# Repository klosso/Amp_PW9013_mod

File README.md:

Base mod for Unitra PW9013 ampituner.
Not any sufifticate thing. Just replace old transistors based eq with Ic and, add BT FM tuner.
Tuner based on FM module RD07 with RDS
Autio IC is old TSA6231.

Versions :
0.00001 preliminary alfa.

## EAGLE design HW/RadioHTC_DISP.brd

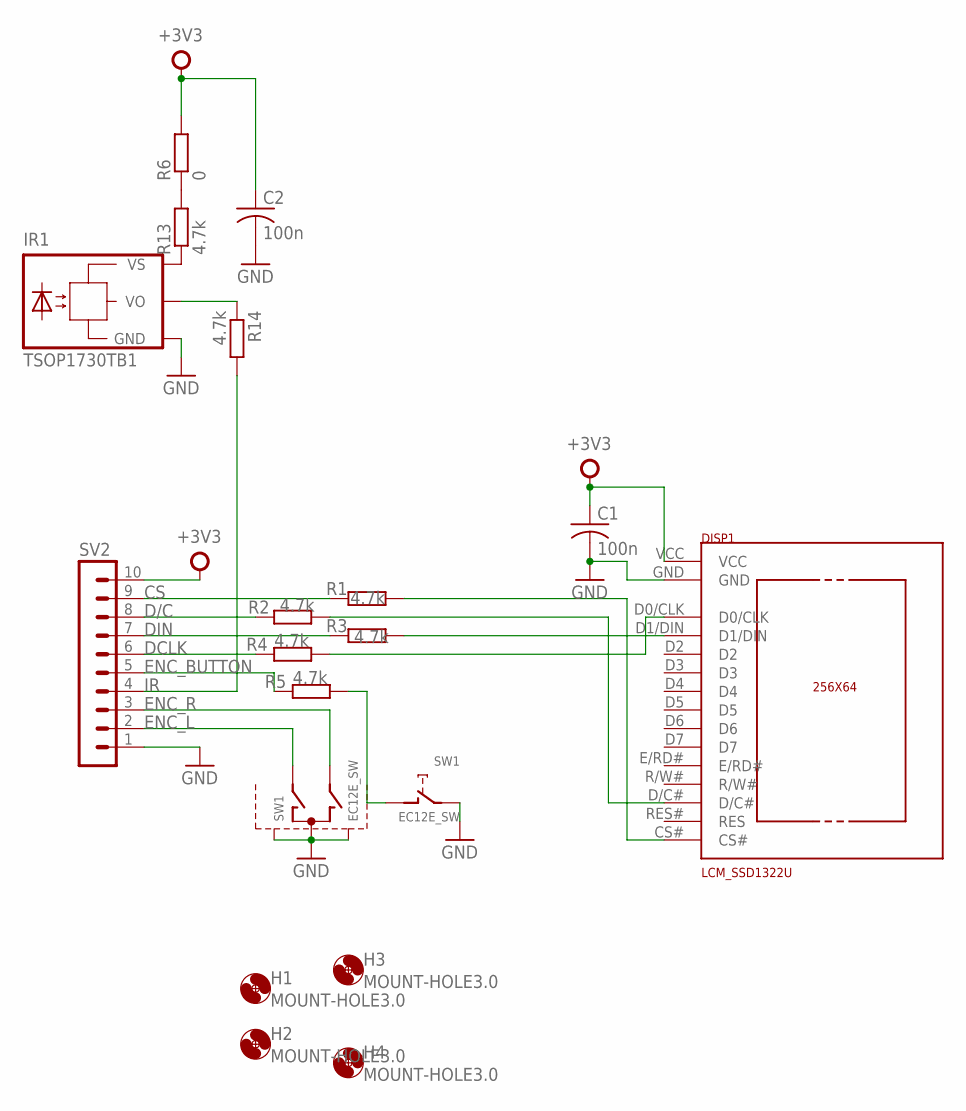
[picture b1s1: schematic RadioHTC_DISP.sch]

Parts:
C1, C2: 100n; C1206
DISP1: LCM_SSD1322U; LCM_SSD1322_VERT
H1, H2, H3, H4: MOUNT-HOLE3.0; 3,0
IR1: TSOP1730TB1; TSOP17_TB1
R1, R2, R3, R4, R5, R13, R14: 4.7k; R1206
R6: 0; R1206
SV2: MA10-1
SW1: EC12E_SW; ALPS_EC12E_SW

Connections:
+3V3: C1.1, C2.1, DISP1.VCC, R6.2, SV2.10
CS: R1.1, SV2.9
CS#: DISP1.CS#, R1.2
D/C: R2.1, SV2.8
DCLK: R4.1, SV2.6
DCLK_: DISP1.D0/CLK, R4.2
DC_: DISP1.D/C#, R2.2
DIN: R3.1, SV2.7
DIN_: DISP1.D1/DIN, R3.2
ENC_BUTTON: R5.1, SV2.5
ENC_L: SV2.2, SW1.A
ENC_R: SV2.3, SW1.B
GND: C1.2, C2.2, DISP1.GND, IR1.GND, SV2.1, SW1.C, SW1.E (2), SW1.GND@1, SW1.GND@2
IR: R14.2, SV2.4
unnamed: R5.2, SW1.D (1)
unnamed: R6.1, R13.2
unnamed: IR1.VS, R13.1
unnamed: IR1.VO, R14.1

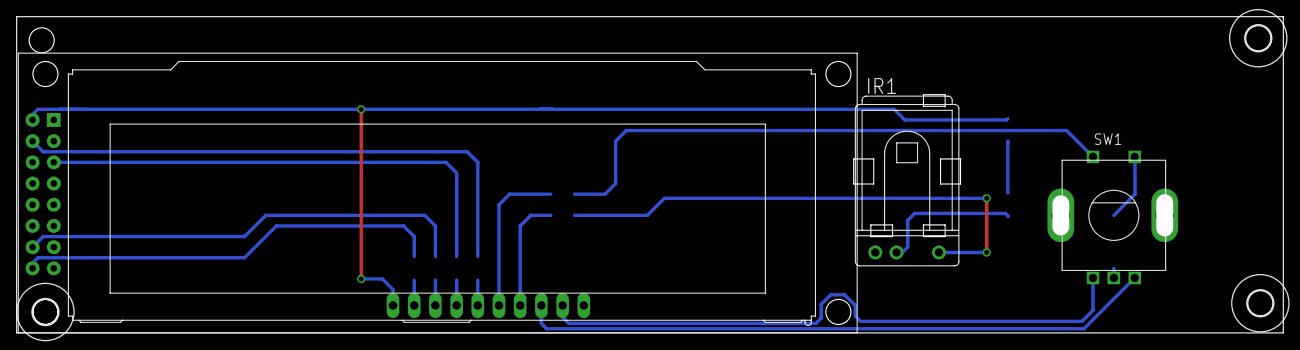
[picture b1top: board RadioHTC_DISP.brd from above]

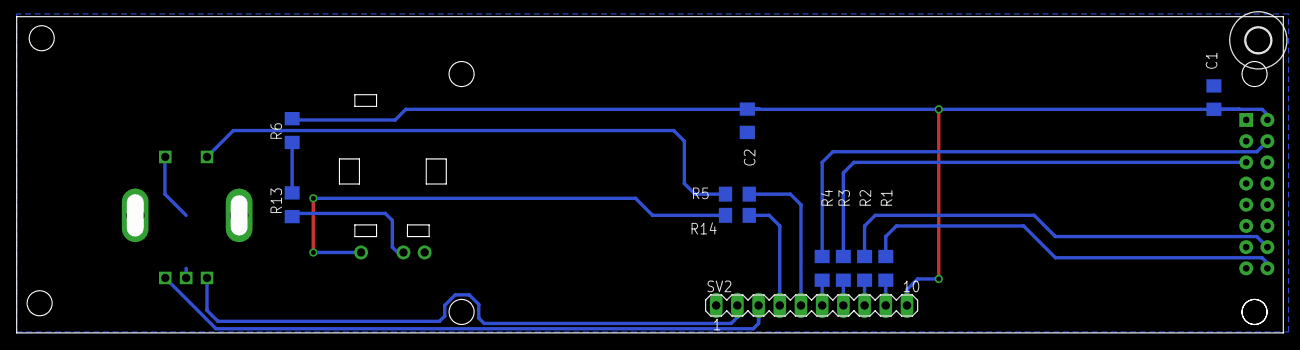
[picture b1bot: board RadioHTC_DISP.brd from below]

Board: 2 copper layers, 149.7 x 35.9 mm, 18 parts (12 on the bottom side), 18 nets.

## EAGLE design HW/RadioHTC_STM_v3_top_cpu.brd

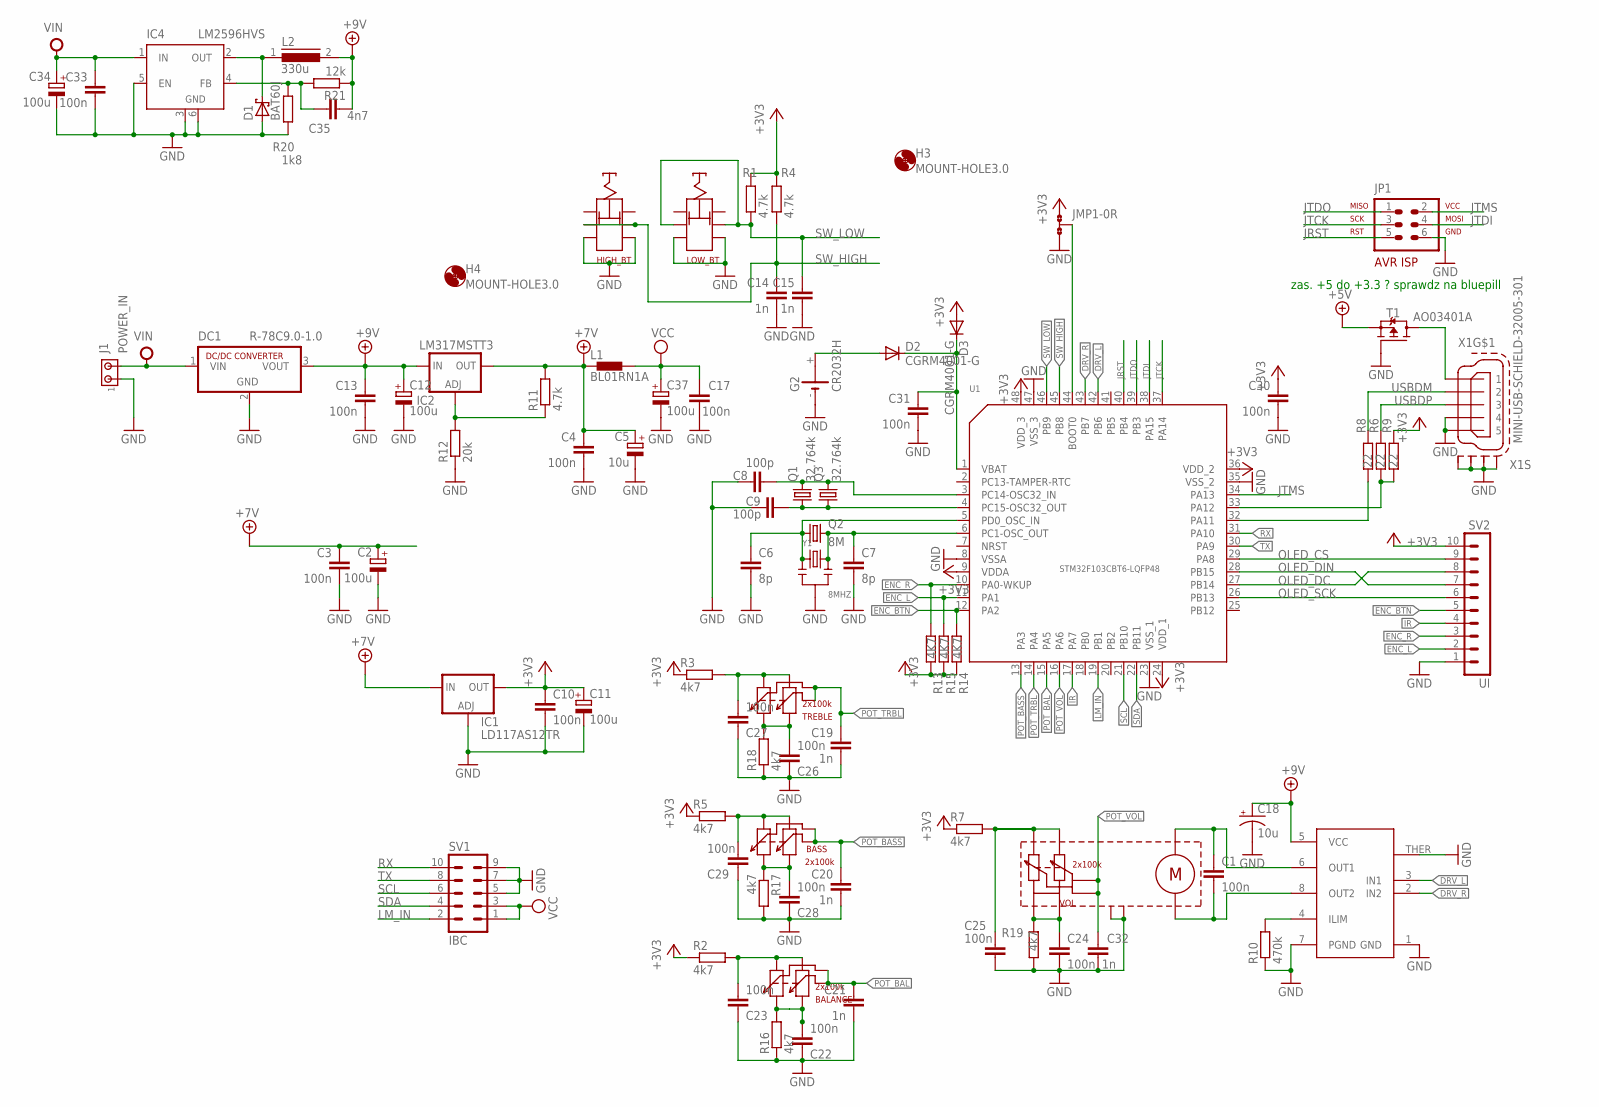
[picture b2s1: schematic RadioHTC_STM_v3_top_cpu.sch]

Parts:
BALANCE: 2x100k; POT_VERT_DOUBLE
BASS: 2x100k; POT_VERT_DOUBLE
C1, C3, C4, C10, C13, C17, C22, C23, C24, C25, C26, C27, C28, C29, C30, C31, C33: 100n; C1206
C2, C11, C34: 100u; E2-5
C5: 10u; E2-5
C6, C7: 8p; C0805K
C8, C9: 100p; C0805K
C12: 100u; 153CLV-0605
C14, C15, C19, C20, C21, C32: 1n; C1206
C18: 10u; 153CLV-0810
C35: 4n7; C1206
C37: 100u; 153CLV-0405
D1: BAT60J; SOD323_ST
D2, D3: CGRM4001-G; SOD-123_MINI-SMA
DC1: R-78C9.0-1.0; SIP3
G2: CR2032H
H3, H4: MOUNT-HOLE3.0; 3,0
IC1: LD117AS12TR; SOT223
IC2: LM317MSTT3; SOT223
IC4: LM2596HVS; TO263-5
J1: POWER_IN; 1X2MTA
JMP1: 0R-JUMPA; A0R-JMP
JP1: AVR-ISP-6VERT; AVR-ISP-6
L1: BL01RN1A
L2: 330u; DR74
Q1: 32.764k; MM39SL
Q2: 8M; HC49U-V
Q3: 32.764k; MM20SS
R1, R4, R11: 4.7k; R1206
R2, R3, R5, R7, R16, R17, R18, R19: 4k7; R1206
R6, R8, R9: 22; R1206
R10: 470k; R1206
R12: 20k; R1206
R13, R14, R15: 4K7; R1206
R20: 1k8; R1206
R21: 12k; R1206
SV1: IBC; ML10
SV2: UI; MA10-1W
SW4: LOW_BT; ISO3
SW6: HIGH_BT; ISO3
T1: AO03401A; SOT23-R
TREBLE: 2x100k; POT_VERT_DOUBLE
U1: STM32F103CBT6-LQFP48; LQFP48-0.5-7X7MM
U2: DRV8871
VOL: 2x100k; POT_DOUBLE_MOTOR
X1: MINI-USB-SCHIELD-32005-301; 32005-301
Y1: 8MHZ; X3-SMD-3.6X1.3X0.8MM

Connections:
+3V3: C10.1, C11.+, C30.1, D3.A, IC1.4 (OUT), JMP1.1, R1.2, R2.1, R3.1, R4.2, R5.1, R7.1, R9.2, R13.2, R14.2, R15.2, SV2.10, U1.9 (VDDA), U1.24 (VDD_1), U1.36 (VDD_2), U1.48 (VDD_3)
+5V: T1.2 (S)
+7V: C2.+, C3.1, C4.1, C5.+, IC1.3 (IN), IC2.4 (OUT), L1.1, R11.2
+9V: C12.+, C13.1, C18.+, C35.2, DC1.3 (VOUT), IC2.3 (IN), L2.2, R21.1, U2.5 (VCC)
DRV_L: U1.42 (PB6), U2.3 (IN1)
DRV_R: U1.43 (PB7), U2.2 (IN2)
ENC_BTN: R14.1, SV2.5, U1.12 (PA2)
ENC_L: R15.1, SV2.2, U1.11 (PA1)
ENC_R: R13.1, SV2.3, U1.10 (PA0-WKUP)
GND: C2.-, C3.2, C4.2, C5.-, C6.2, C7.2, C8.2, C9.1, C10.2, C11.-, C12.-, C13.2, C14.2, C15.2, C17.2, C18.-, C19.2, C20.2, C21.2, C22.1, C23.1, C24.1, C25.1, C26.1, C27.1, C28.1, C29.1, C30.2, C31.2, C32.2, C33.2, C34.-, C37.-, D1.A, DC1.2 (GND), G2.-, IC1.1 (ADJ), IC4.3 (GND), IC4.5 (EN), IC4.6 (GND), J1.1, JMP1.3, JP1.6, R10.1, R12.1, R16.1, R17.2, R18.1, R19.1, R20.1, SV1.5, SV1.7, SV1.9, SV2.1, SW4.P$3, SW4.P$4, SW6.P$3, SW6.P$4, T1.1 (G), U1.8 (VSSA), U1.23 (VSS_1), U1.35 (VSS_2), U1.47 (VSS_3), U2.1 (GND), U2.7 (PGND), U2.THER (GND), VOL.P$9 (G), VOL.P$10 (G), X1.4, X1.5, X1.M1 (S1), X1.M2 (S2), X1.M3 (S3), X1.M4 (S4), Y1.2
IR: SV2.4, U1.17 (PA7)
JRST: JP1.5, U1.40 (PB4)
JTCK: JP1.3, U1.37 (PA14)
JTDI: JP1.4, U1.38 (PA15)
JTDO: JP1.1, U1.39 (PB3)
JTMS: JP1.2, U1.34 (PA13)
LM_IN: SV1.2, U1.19 (PB1)
unnamed: R10.2, U2.4 (ILIM)
unnamed: C6.1, Q2.1, U1.5 (PD0_OSC_IN), Y1.1
unnamed: T1.3 (D), X1.1
unnamed: IC2.1 (ADJ), R11.1, R12.2
unnamed: C7.1, Q2.2, U1.6 (PC1-OSC_OUT), Y1.3
unnamed: C9.2, Q1.1, Q3.1, U1.4 (PC15-OSC32_OUT)
unnamed: JMP1.2, U1.44 (BOOT0)
unnamed: C8.1, Q1.4 (2), Q3.4 (2), U1.3 (PC14-OSC32_IN)
unnamed: C35.1, IC4.4 (FB), R20.2, R21.2
unnamed: R6.1, R9.1, U1.33 (PA12)
unnamed: C31.1, D2.C, D3.C, U1.1 (VBAT)
unnamed: D2.A, G2.+
unnamed: R8.1, U1.32 (PA11)
unnamed: BASS.B1, BASS.B2, C28.2, R17.1
unnamed: D1.C, IC4.2 (OUT), L2.1
unnamed: BASS.A1, BASS.A2, C29.2, R5.2
unnamed: C24.2, R19.2, VOL.P$5, VOL.P$6
unnamed: BALANCE.B1, BALANCE.B2, C22.2, R16.2
unnamed: C26.2, R18.2, TREBLE.B1, TREBLE.B2
unnamed: C27.2, R3.2, TREBLE.A1, TREBLE.A2
unnamed: BALANCE.A1, BALANCE.A2, C23.2, R2.2
unnamed: C1.1, U2.6 (OUT1), VOL.M+
unnamed: C1.2, U2.8 (OUT2), VOL.M-
unnamed: C25.2, R7.2, VOL.P$2, VOL.P$3
OLED_CS: SV2.9, U1.29 (PA8)
OLED_DC: SV2.8, U1.27 (PB14)
OLED_DIN: SV2.7, U1.28 (PB15)
OLED_SCK: SV2.6, U1.26 (PB13)
POT_BAL: BALANCE.C1, BALANCE.C2, C21.1, U1.15 (PA5)
POT_BASS: BASS.C1, BASS.C2, C20.1, U1.13 (PA3)
POT_TRBL: C19.1, TREBLE.C1, TREBLE.C2, U1.14 (PA4)
POT_VOL: C32.1, U1.16 (PA6), VOL.P$4, VOL.P$7
RX: SV1.10, U1.31 (PA10)
SCL: SV1.6, U1.21 (PB10)
SDA: SV1.4, U1.22 (PB11)
SW_HIGH: C14.1, R4.1, SW6.P$2, SW6.P$5, U1.45 (PB8)
SW_LOW: C15.1, R1.1, SW4.P$2, SW4.P$5, U1.46 (PB9)
TX: SV1.8, U1.30 (PA9)
USBDM: R8.2, X1.2
USBDP: R6.2, X1.3
VCC: C17.1, C37.+, L1.2, SV1.1, SV1.3
VIN: C33.1, C34.+, DC1.1 (VIN), IC4.1 (IN), J1.2

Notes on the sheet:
zas. +5 do +3.3 ? sprawdz na bluepill

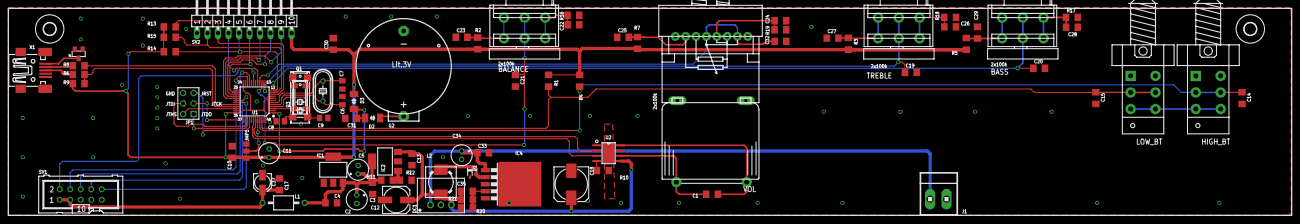
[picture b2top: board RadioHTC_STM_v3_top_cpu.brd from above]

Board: 2 copper layers, 310.0 x 50.0 mm, 87 parts (1 on the bottom side), 58 nets.

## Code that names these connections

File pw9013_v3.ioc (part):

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Mcu.Name=STM32F103C(8-B)Tx
Mcu.Package=LQFP48
Mcu.UserName=STM32F103CBTx
PA0-WKUP.GPIOParameters=GPIO_Label
PA0-WKUP.GPIO_Label=ENC_L
PA0-WKUP.Signal=S_TIM2_CH1_ETR
PA1.GPIOParameters=GPIO_Label
PA1.GPIO_Label=ENC_R
PA1.Signal=S_TIM2_CH2
PA10.Mode=Asynchronous
PA10.Signal=USART1_RX
PA11.Mode=Device
PA11.Signal=USB_DM
PA12.Mode=Device
PA12.Signal=USB_DP
PA13.Mode=Serial_Wire
PA13.Signal=SYS_JTMS-SWDIO
PA14.Mode=Serial_Wire
PA14.Signal=SYS_JTCK-SWCLK
PA2.GPIOParameters=GPIO_Label
PA2.GPIO_Label=ENC_BTN
PA2.Signal=GPIO_Input
PA3.GPIOParameters=GPIO_Label
PA3.GPIO_Label=BASS
PA3.Signal=ADCx_IN3
PA4.GPIOParameters=GPIO_Label
PA4.GPIO_Label=TRBL
PA4.Signal=ADCx_IN4
PA5.GPIOParameters=GPIO_Label
PA5.GPIO_Label=BLNC
PA5.Signal=ADCx_IN5
PA6.GPIOParameters=GPIO_Label
PA6.GPIO_Label=VOL
PA6.Signal=ADCx_IN6
PA7.Signal=S_TIM3_CH2
PA8.GPIOParameters=GPIO_Label
PA8.GPIO_Label=OLED_CS
PA8.Signal=GPIO_Output
PA9.Mode=Asynchronous
PA9.Signal=USART1_TX
PB1.GPIOParameters=GPIO_Label
PB1.GPIO_Label=LM_IN
PB1.Signal=ADCx_IN9
PB10.Mode=I2C
PB10.Signal=I2C2_SCL
PB11.Mode=I2C
PB11.Signal=I2C2_SDA
PB13.Mode=TX_Only_Simplex_Unidirect_Master
PB13.Signal=SPI2_SCK
PB14.GPIOParameters=GPIO_Label
PB14.GPIO_Label=OLED_DC
PB14.Signal=GPIO_Output
PB15.Mode=TX_Only_Simplex_Unidirect_Master
PB15.Signal=SPI2_MOSI
PB6.GPIOParameters=GPIO_Label
PB6.GPIO_Label=DRV_L
PB6.Signal=GPIO_Output
PB7.GPIOParameters=GPIO_Label
PB7.GPIO_Label=DRV_R
PB7.Signal=GPIO_Output
PB8.GPIOParameters=GPIO_Label
PB8.GPIO_Label=SW_HIGH
PB8.Signal=GPIO_Input
PB9.GPIOParameters=GPIO_Label
PB9.GPIO_Label=SW_LOW
PB9.Signal=GPIO_Input
PC14-OSC32_IN.Mode=LSE-External-Oscillator
PC14-OSC32_IN.Signal=RCC_OSC32_IN
PC15-OSC32_OUT.Mode=LSE-External-Oscillator
PC15-OSC32_OUT.Signal=RCC_OSC32_OUT
PD0-OSC_IN.Mode=HSE-External-Oscillator
PD0-OSC_IN.Signal=RCC_OSC_IN
PD1-OSC_OUT.Mode=HSE-External-Oscillator
PD1-OSC_OUT.Signal=RCC_OSC_OUT
RCC.SYSCLKFreq_VALUE=48000000
RCC.SYSCLKSource=RCC_SYSCLKSOURCE_PLLCLK
board=custom

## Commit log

2022-12-31 add HW documentation
